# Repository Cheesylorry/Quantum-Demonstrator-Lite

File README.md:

# Quantum-Demonstrator-Lite
A Plug and play Quantum Algorithm Demonstrator for Students. Integrates into QuBeads, a software for visualising up to three Qubits, with fully customisable Quantum Gates.

*Picture of the Setup used at the Max Planck Institute of Quantum Optics*

The Quantum Demonstrator Lite can be used to demonstrate algorithms up to three Qubits over seven positions, and these can be viewed in Detail with the  QuBeads Software, available at https://spindrops.org/2.5.0-beta1/download.html *(We recommend going with the Beta, as it has the updated visualisation)*

    NOTE: The final product is to be used with QuBeads, the successor to SpinDrops. The auto Update is not available in SpinDrops but is on the ToDo for QuBeads.

The Quantum Demontrator Lite utilises 21 RC522 readers to maximise flexibility with the Quantum gates, allowing you to create your own custom gates. These are being controlled by a Raspberry Pi Pico2 Microcontroller, which in turn communicates with the PC over USB. 

It was designed to be somewhat affordable to institutions and Schools, with a price around 400€ depending of the suppliers you choose, and the means of assembly.

# Getting Started
For anybody wanting to build the Demonstrator, you should have a few prerequisite Tools:
| Tool | |
| --- | --- |
| 3D Printer | Ideally one with a Printbed bigger than 300x250, but 250x250 can also accomodate all parts. The ability to Print Mulit Colour is also very Helpful for printing the Gates|
| Soldering Iron | A fine tipped Soldering Station/Iron is necesary, should you decide to assemble the PCB yourself, Solder flux, tweezers, tin snips and more standard Soldering tools are required|
| Hex Bits | A standard Metric Set of Hex bits |

*Note: Should you decide to assemble the PCB yourself, be aware the SMD components are not the easiest to work with. A revamped version is a WIP which will drastically reduce the amount of components needed*

## Electronics
|[`Electronics/`](Electronics/README.md) contains the PCB Schematic and Board design. The PCB was designed in KiCad.
Parts needed for the PCB can be found via the Schematics, the BOM or here.

### Main PCB (Current state)
The current State is functional, but a simpler V2 is being worked on.

The Main PCB contains the Raspberry Pi Pico and all the power conversion needed to power the NFC readers, the LEDs and the Pi Pico itself.

| ID | Designator | Value/Component | Footprint | Qty | Source | Cost |
|:---:|:---|:---|:---|:---:|:---|:---:|
| 1 | A2 | Rapberry Pi Pico 2 | Pico SMD | 1 | [Conrad](https://www.conrad.de/de/p/raspberry-pi-pico-2-mikrocontroller-pico-2-3305690.html) | 5€ |
| 2 | Cbst1, Cbst2 | 100nF | 0805 SMD | 2 | [Supplier](URL) | |
| 3 | Cin1, Cin2  Cin3, Cin4 | 10µF | 0805 SMD | 4 | [Supplier](URL) | |
| 4 | Cout1, Cout2, Cout3 | 22µF | 0603 SMD | 3 | [Supplier](URL) | |
| 5 | Cout4 | 47µF | 1206 SMD | 1 | [Supplier](URL) | |
| 6 | F1 | 5A Fuse | 1206 SMD | 1 | [Supplier](URL) | |
| 7 | J1 | USB-C 16Pin | USB-C 16P | 1 | [Supplier](URL) | |
| 8 | J4 | Barrel Jack | Barrel Jack | 1 | [Digikey](https://www.digikey.de/de/products/detail/w%C3%BCrth-elektronik/694106301002/5047522?s=N4IgTCBcDaIGwE4AsBGADHAzG9aIF0BfIA) | 1€ |
| 9 | L1 | 2.2µH | ANR6045 SMD | 1 | [Supplier](URL) | |
| 10 | L2 | 4.7µH | 1008 SMD | 1 | [Supplier](URL) | |
| 11 | PCBconn1.1–3.2 | Molex Miligrid 4x2 | 08x04 THT | 4 | [Digikey](https://www.digikey.de/de/products/detail/molex/0878310820/679677) | 7,50€ |
| 12 | PCBconn1.1–3.2 | Molex Miligrid 4x2 | 08x04 THT | 2 | [Digikey](https://www.digikey.de/de/products/detail/molex/0878330831/2405183) | 5€ |
| 13 | R1, R2 | 5.1kΩ | 0805 SMD | 1 | [Supplier](URL) | |
| 14 | R3 | 160 Ω | 0805 SMD | 1 | [Supplier](URL) | |
| 15 | R6 | 100kΩ | 0805 SMD | 1 | [Supplier](URL) | |
| 16 | Rfbb1, Rfbb2 | 10kΩ | 0805 SMD | 2 | [Supplier](URL) | |
| 17 | Rfbt1 | 33.2kΩ | 0805 SMD | 1 | [Supplier](URL) | |
| 18 | Rfbt2 | 56.2kΩ | 0805 SMD | 1 | [Supplier](URL) | |
| 19 | SW2 | Switch with LED | R1966 SW SMD | 1 | [Digikey](https://www.digikey.de/de/products/detail/e-switch/R1966ABLKBLKESRED/251346?s=N4IgTCBcDaIEoEYCcA2FBBAQgGQNI9wFEBlOQgERAF0BfIA) | 2,50€ |
| 20 | U1 | TPS563200DDCR | SOT-23-6 SMD | 1 | [Supplier](URL) | |
| 21 | U2 | TPS561201DDCR | SOT-23-6 SMD | 1 | [Supplier](URL) | |

For a complete PCB assembbly service, you can expect to pay ~85€ 

Parts 1, 8, 11, 12 and 19 will have to be hand soldered. Numbers 8, 9 and 12 are Normal THT components, 19 has to be wired and then soldered.
The Raspberry Pi Pico2 has an Unusual way of soldering it to the PCB, due to the assumption one doesn't have a hotplate available.

| Top Side | Bottom Side |
|:--:|:--:|
||
||*Marked by the red Arrow are two through Holes, **these must be kept unfilled**, double check this when ordering the PCB* 

First solder down two of the SMD Pads of the Pi Pico, then turn the board around and fill the Marked through holes with solder, make sure to keep it warm for a bit, and probe the PCB for connection between the USB and the data pins on the Pi Pico.

### Connecting PCBs
The Quantum Demonstrator uses three almost identical PCBs to connect the individual NFC Readers to the Main PCB. These Connecting PCBs also mount the LEDs for the illumination. While all of the Connecting PCBs are the same, the Placement of the connectors is different for one of the three boards. 
These connectors are labeled with A.1, A.2 and B.1, B.2. This is neccessary due to cabeling and space saving.

**Two Boards must be configured with the A.1 and A.2 ports soldered and one Board with the B.1 and B.2 ports**

For all three Connection PCB, you will need:
| ID | Designator | Value/Component | Footprint | Qty | Source | Cost |
|:---:|:---|:---|:---|:---:|:---|:---:|
| 1 | LEDStrip1 5m | WS2815 12V LED Strip | 500x10mm | 1 | [Amazon](https://www.amazon.de/-/en/SEZO-Upgraded-Individually-Addressable-Non-Waterproof/dp/B0DNHVZDY6?) | 25€ |
| 2 | J2-J9 | Conn\_01x08\_Socket | THT | 30 | [Conrad](https://www.conrad.de/de/p/mpe-garry-stiftleiste-standard-anzahl-reihen-1-polzahl-je-reihe-8-087-1-008-0-s-xs0-1260-1-st-734023.html) | 5,50€ |
| 3 | PCBconnA.1 - A.2 | Conn\_02x04\_Counter\_Clockwise | THT | 6 | [Digikey](https://www.digikey.de/de/products/detail/molex/0878330831/2405183) | 13€ |

### Miscelaneous Parts
*Important Note for the NFC readers: **These must be the JoyIT readers, as the pinout is not compatible between different vendors.** The ones we specify have to have straight Through hole connectors, you can desolder the included conneectors or order via JoyIT directly and ask to have these connectors omitted, such that you can solder your own.*

| ID | Designator | Value/Component | Qty | Source | Cost |
|:---:|:---|:---|:---:|:---|:---:|
| 1 | NFC Reader | JoyIT RC522 | 21 | [Conrad](https://www.conrad.de/de/p/joy-it-sbc-rfid-rc522-rfid-set-1-st-1503746.html) | 112€ |
| 2 | Cables 218509-1083 | Molex Milligrid 02x08 locking | 6 | [Mouser](https://www.mouser.de/en/ProductDetail/Molex/218509-1083?qs=A6eO%252BMLsxmQCsrsfTUrgcg%3D%3D) | 25,15€ |
| 3 | NFC Tags | 38 mm - NTAG 213 - 180 Byte | 50 | [NFC-Tag-Shop](https://www.nfc-tag-shop.de/en/NFC-Sticker-PET-38-mm-NTAG-213-180-Byte-white/68261) | 29,50€ |

## Mechanical Construction
The Case for the Quantum Demonstrator is Mostly 3D Printed, with two extra Aluminium Extrusions for stability. 

Rccommended Print settings:
| | | | | | |
|:---|:---:|:---|:---:|:---|:---:|
| Material: | PLA or PETG | Print Bed: | Satin or Textured | Infill: | 10-15% Gyroid|
| Nozzle Size: | 0.4mm | Layer height: | 0.15mm | Supports: | Only on bed |

### Bill of Materials
| Item | Quantity | Description | Suplier | Costs |
|:---:|:---:|:---|:---|:---:|
| 1 | 1 | PCB Main | | 100€ |
| 2 | 3 | Conn PCB | | 43€ |
| 3 | 1 | Switch | | 2,50€ |
| 4 | 2 | 594 mm 2020 Profile| [Motedis](https://www.motedis.com/de/Aluprofil-20x20-B-Typ-Nut-6) | 9€ |
| 5 | 1 | 🔴 Front Centre | | |
| 6 | 1 | 🔴 Middle Centre | | |
| 7 | 1 | 🔴 Rear Centre | | |
| 8 | 1 | 🔴 Corner Shoulder 1 | | |
| 9 | 1 | 🔴 Middle Shoulder 1 | | |
| 10 | 2 | 🔴 Corner Shoulder 2 | | |
| 11 | 1 | 🔴 Corner Shoulder 3 | | |
| 12 | 1 | 🔴 Middle Shoulder 2 | | |
| 13 | 3 | 🔴 Feet | | |
| 14 | 1 | 🔴 Lid Part 1/3 | | |
| 15 | 1 | 🔴 Lid Part 3/1 | | |
| 16 | 1 | 🔴 Lid Part 2 | | |
| 17 | 31 | Hex screw M4x0.70 x 12 A2 | [Motedis](https://www.motedis.com/de/Zylinderschraube-mit-Innensechskant-nach-DIN-912/M4x12) | 4,17€ |
| 18 | 6 | Hex socket head cap screw M4x0.70 x 40 A2 | [Motedis](https://www.motedis.com/de/Sonderschraube-Stossverbinder-M4x40-180G-N5-I-Typ) | 1,70€ |
| 19 | 12 | Hex countersunk screw M4x0.70 x10 A2 | [Motedis](https://www.motedis.com/de/Senkschraube-mit-Innensechskant-nach-DIN-7991/M4x10) | 3,17€ |
| 20 | 2 | 🔴 Lidholder type 1 | | |
| 21 | 2 | 🔴 Lidholder type 2 | | |
| 22 | 2 | 🔴 Lidholder type 3 | | |
| 23 | 2 | PETG 3D-printing Filament | [Prusa3D]({https://www.prusa3d.com/product/prusament-petg-prusa-galaxy-black-1kg-nfc) | 58€ |
| 24 | 39 | Heatset Insert M4| [CNC Kitchen](https://cnckitchen.store/products/heat-set-insert-m4-x-4-short-version-100-pieces)|9,40€|
| 25 | xx | Heatset Insert M2|||
| 26 | xx | T-Nut6-M4  Bosch Rexroth compatible|||

*BOM of Assembly 1, List of Parts to 3D print marked in (🔴)*

*Todo: Link Parts in here to parts in Project*

On the Prusa XL this would need 4-5 Printbeds

## Assembly of the Case

### Heatset Inserts
In preperation for assembly, insert the threaded Heatset Inserts into the pre made holes.
For this set your soldering iron to aroun 250°C and slowly but firmly melt and press the insert into the hole. Try to keep it as level as possible to the Surface. The Following pcitures show where to position the Inserts.
| Top Side | Bottom Side |
|:--:|:--:|
||

### Connection to the Aluminium Extrusion

There are multiple screwholes from the outside accessing the Aluminium extrusion. Insert the Matching screw, at a T-Nut onto it, and slide it onto the Aluminium Extrusion. 
Start with the Shoulder Sections, then do the middle section, then the Feet to tie it all to gether. Only put the lid on right at the end.

### Mounting of PCBs
The Connection PCBs are screwed down with three M4 Screws, while the Main PCB is screwed down with three M2 screws.

### Installing LEDs
Glue the LED strip down on the marked region. Make sure the Pinout is correct, adn solder it to the given Pads.
To aid in diffusion a Thin plastic sheet is glued to the back of the Lid pieced to coder the Lighting slits (A piece of paper also works).

## Software
The Quantum Demonstrator requires some Embedded and some PC side software. 
### Prerequisites
| Software | |
| --- | --- |
| PlatformIO | A means to flash the C++ onto the RaspberryPi Pico via USB e.g. PlatformIO in VSCodium|
| Python 3.14| or newer. Needed for the PC Side software
| Tkinter 3.14 | or newer. Needed for the GUI on the PC side|

### Embedded Software
Flash the C++ Program [`main.cpp`](Embedded_Software/src/main.cpp) onto the Raspberry Pi Pico 2 via USB. 

### PC Side Software 
Download the [`PC_side_Software/`](/PC_side_Software/README.md) folder and run 

    python main.py          

Quick check without hardware or GUI:

    python selftest.py

**For a more in depth explaination:** [`/PC_side_Software/README.md`](/PC_side_Software/README.md)

## Constructing the Quantum Gates
Download the desired Gates from [`/CAD files/Quantum Gates/`](/CAD%20files/Quantum%20Gates/) and 3D print them. Then glue An NFC Tag into each Indent (on single Qubit gates only one, on Mulit Qubit gates two or even three)

# Using the Quantum Demonstrator (Work in Progress)
Connect the Demonstrator to 12V power and USB, and Turn it on
Start python main.py and select the USB device in the dropdown Menu, and check if you can see Gates appear when you place them on the readers.

"The Autowrite Json" automatically writes the JSON ever time an update is registered. This means you can continously import these files into spindrops.The directroy it deposits the files in can be chosen on launch.
Now Start spindrops and import the newly generated QD_output.json File.
Congratulations! You now have a functioning Quantum Demonstrator.

# Enrolling New Gates into the Database (Heavy Work in Progress)
Run
    python enroll.py --port /dev/ttyACM0
and then follow the instructions. The Names are only Important if you want to designate your own gates via the spin drops Syntax.

| Real World Gate | Database Shortname to use|
| --- | --- |
| Hadamard | **H**|
| Not | **X** |
| Phase | **Phase(*[deg]*)**|
| | | 

# Known Issues / ToDo
When enrolling gates the UUID gets entered incorrectly. *Fix: Use multiple reads and verify against each other* - Temporary fix, reenroll the gate.

## ToDo
- Add GUI to the enroll process
- Fix framing issues in gui.py
- Package as Binary
- Proper spindrops integration -> WIP

# Revamped PCB (HEAVY WIP)
to lower the costs of single piece production move from custom designed Voltage conversion to premade TRACOS.

Staged Design 12V -> 5V -> 3.3? vs Drirect Design 12V -> 5V and 12V -> 3.3V

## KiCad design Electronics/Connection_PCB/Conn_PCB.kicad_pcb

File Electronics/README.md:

Parts needed for the PCB can be found via the Schematics, the BOM or here.

| ID | Designator | Value/Component | Footprint | Qty | Source | Cost |
|:---:|:---|:---|:---|:---:|:---|:---:|
| 1 | A2 | Rapberry Pi Pico 2 | Pico SMD | 1 | [Conrad](https://www.conrad.de/de/p/raspberry-pi-pico-2-mikrocontroller-pico-2-3305690.html) | 5€ |
| 2 | Cbst1, Cbst2 | 100nF | 0805 SMD | 2 | [Supplier](URL) | |
| 3 | Cin1, Cin2  Cin3, Cin4 | 10µF | 0805 SMD | 2 | [Supplier](URL) | |
| 4 | Cout1, Cout2, Cout3 | 22µF | 0603 SMD | 3 | [Supplier](URL) | |
| 5 | Cout4 | 47µF | 1206 SMD | 1 | [Supplier](URL) | |
| 6 | F1 | 5A Fuse | 1206 SMD | 1 | [Supplier](URL) | |
| 7 | J1 | USB-C 16Pin | USB-C 16P | 1 | [Supplier](URL) | |
| 8 | J4 | Barrel Jack | Barrel Jack | 1 | [Digikey](https://www.digikey.de/de/products/detail/w%C3%BCrth-elektronik/694106301002/5047522?s=N4IgTCBcDaIGwE4AsBGADHAzG9aIF0BfIA) | 1€ |
| 9 | L1 | 2.2µH | ANR6045 SMD | 1 | [Supplier](URL) | |
| 10 | L2 | 4.7µH | 1008 SMD | 1 | [Supplier](URL) | |
| 11 | PCBconn1.1–3.2 | Molex Miligrid 4x2 | 08x04 THT | 4 | [Digikey](https://www.digikey.de/de/products/detail/molex/0878310820/679677) | 7,50€ |
| 12 | PCBconn1.1–3.2 | Molex Miligrid 4x2 | 08x04 THT | 2 | [Digikey](https://www.digikey.de/de/products/detail/molex/0878330831/2405183) | 5€ |
| 13 | R1, R2 | 5.1kΩ | 0805 SMD | 1 | [Supplier](URL) | |
| 14 | R3 | 160 Ω | 0805 SMD | 1 | [Supplier](URL) | |
| 15 | R6 | 100kΩ | 0805 SMD | 1 | [Supplier](URL) | |
| 16 | Rfbb1, Rfbb2 | 10kΩ | 0805 SMD | 2 | [Supplier](URL) | |
| 17 | Rfbt1 | 33.2kΩ | 0805 SMD | 1 | [Supplier](URL) | |
| 18 | Rfbt2 | 56.2kΩ | 0805 SMD | 1 | [Supplier](URL) | |
| 19 | SW2 | Switch with LED | R1966 SW SMD | 1 | [Digikey](https://www.digikey.de/de/products/detail/e-switch/R1966ABLKBLKESRED/251346?s=N4IgTCBcDaIEoEYCcA2FBBAQgGQNI9wFEBlOQgERAF0BfIA) | 2,50€ |
| 20 | U1 | TPS563200DDCR | SOT-23-6 SMD | 1 | [Supplier](URL) | |
| 21 | U2 | TPS561201DDCR | SOT-23-6 SMD | 1 | [Supplier](URL) | |

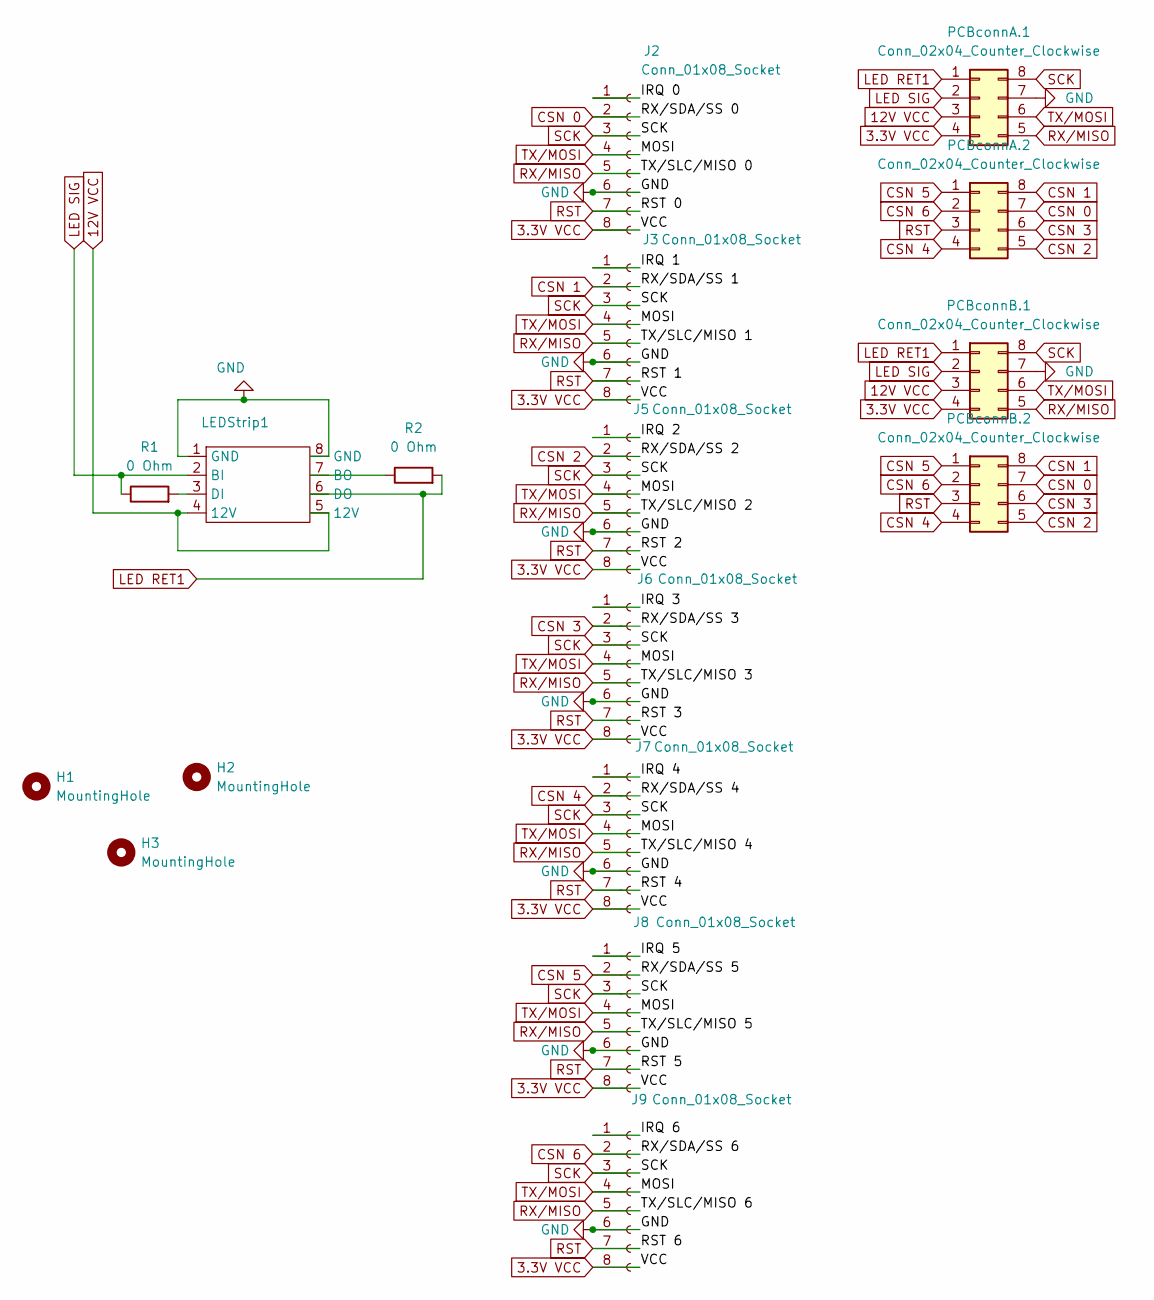
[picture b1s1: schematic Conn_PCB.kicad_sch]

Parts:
H1, H2: MountingHole; MountingHole_4.3x6.2mm_M4_Pad_Via
H3: MountingHole; MountingHole_4.3mm_M4_ISO14580_Pad
J2, J3, J5, J6, J7, J8, J9: Conn_01x08_Socket; PinSocket_1x08_P2.54mm_Vertical
LEDStrip1: LED strip Pad 2815
PCBconnA.1, PCBconnA.2: Conn_02x04_Counter_Clockwise; CONN08_878310820_MOL_Milli_grid
PCBconnB.1, PCBconnB.2: Conn_02x04_Counter_Clockwise; CONN08_878310820_MOL_Milli_grid
R1, R2: 0 Ohm; R_0603_1608Metric_Pad0.98x0.95mm_HandSolder

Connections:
3.3V VCC: J2.8, J3.8, J5.8, J6.8, J7.8, J8.8, J9.8, PCBconnA.1.4, PCBconnB.1.4
12V VCC: LEDStrip1.4 (12V), LEDStrip1.5 (12V), PCBconnA.1.3, PCBconnB.1.3
/IRQ 0: J2.1
/IRQ 1: J3.1
/IRQ 2: J5.1
/IRQ 3: J6.1
/IRQ 4: J7.1
/IRQ 5: J8.1
/IRQ 6: J9.1
CSN 0: J2.2, PCBconnA.2.7, PCBconnB.2.7
CSN 1: J3.2, PCBconnA.2.8, PCBconnB.2.8
CSN 2: J5.2, PCBconnA.2.5, PCBconnB.2.5
CSN 3: J6.2, PCBconnA.2.6, PCBconnB.2.6
CSN 4: J7.2, PCBconnA.2.4, PCBconnB.2.4
CSN 5: J8.2, PCBconnA.2.1, PCBconnB.2.1
CSN 6: J9.2, PCBconnA.2.2, PCBconnB.2.2
GND: J2.6, J3.6, J5.6, J6.6, J7.6, J8.6, J9.6, LEDStrip1.1 (GND), LEDStrip1.8 (GND), PCBconnA.1.7, PCBconnB.1.7
LED RET1: LEDStrip1.6 (DO), PCBconnA.1.1, PCBconnB.1.1, R2.2
LED SIG: LEDStrip1.2 (BI), PCBconnA.1.2, PCBconnB.1.2, R1.1
unnamed: LEDStrip1.7 (BO), R2.1
unnamed: LEDStrip1.3 (DI), R1.2
RST: J2.7, J3.7, J5.7, J6.7, J7.7, J8.7, J9.7, PCBconnA.2.3, PCBconnB.2.3
RX/MISO: J2.5, J3.5, J5.5, J6.5, J7.5, J8.5, J9.5, PCBconnA.1.5, PCBconnB.1.5
SCK: J2.3, J3.3, J5.3, J6.3, J7.3, J8.3, J9.3, PCBconnA.1.8, PCBconnB.1.8
TX/MOSI: J2.4, J3.4, J5.4, J6.4, J7.4, J8.4, J9.4, PCBconnA.1.6, PCBconnB.1.6

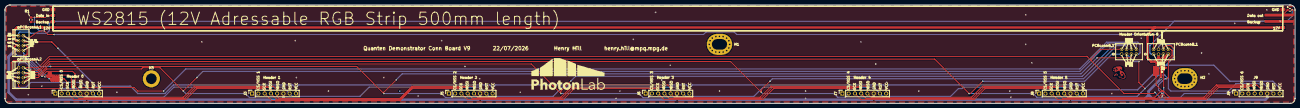
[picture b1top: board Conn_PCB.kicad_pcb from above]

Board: 2 copper layers, 524.5 x 40.0 mm, 17 parts (0 on the bottom side), 18 nets.

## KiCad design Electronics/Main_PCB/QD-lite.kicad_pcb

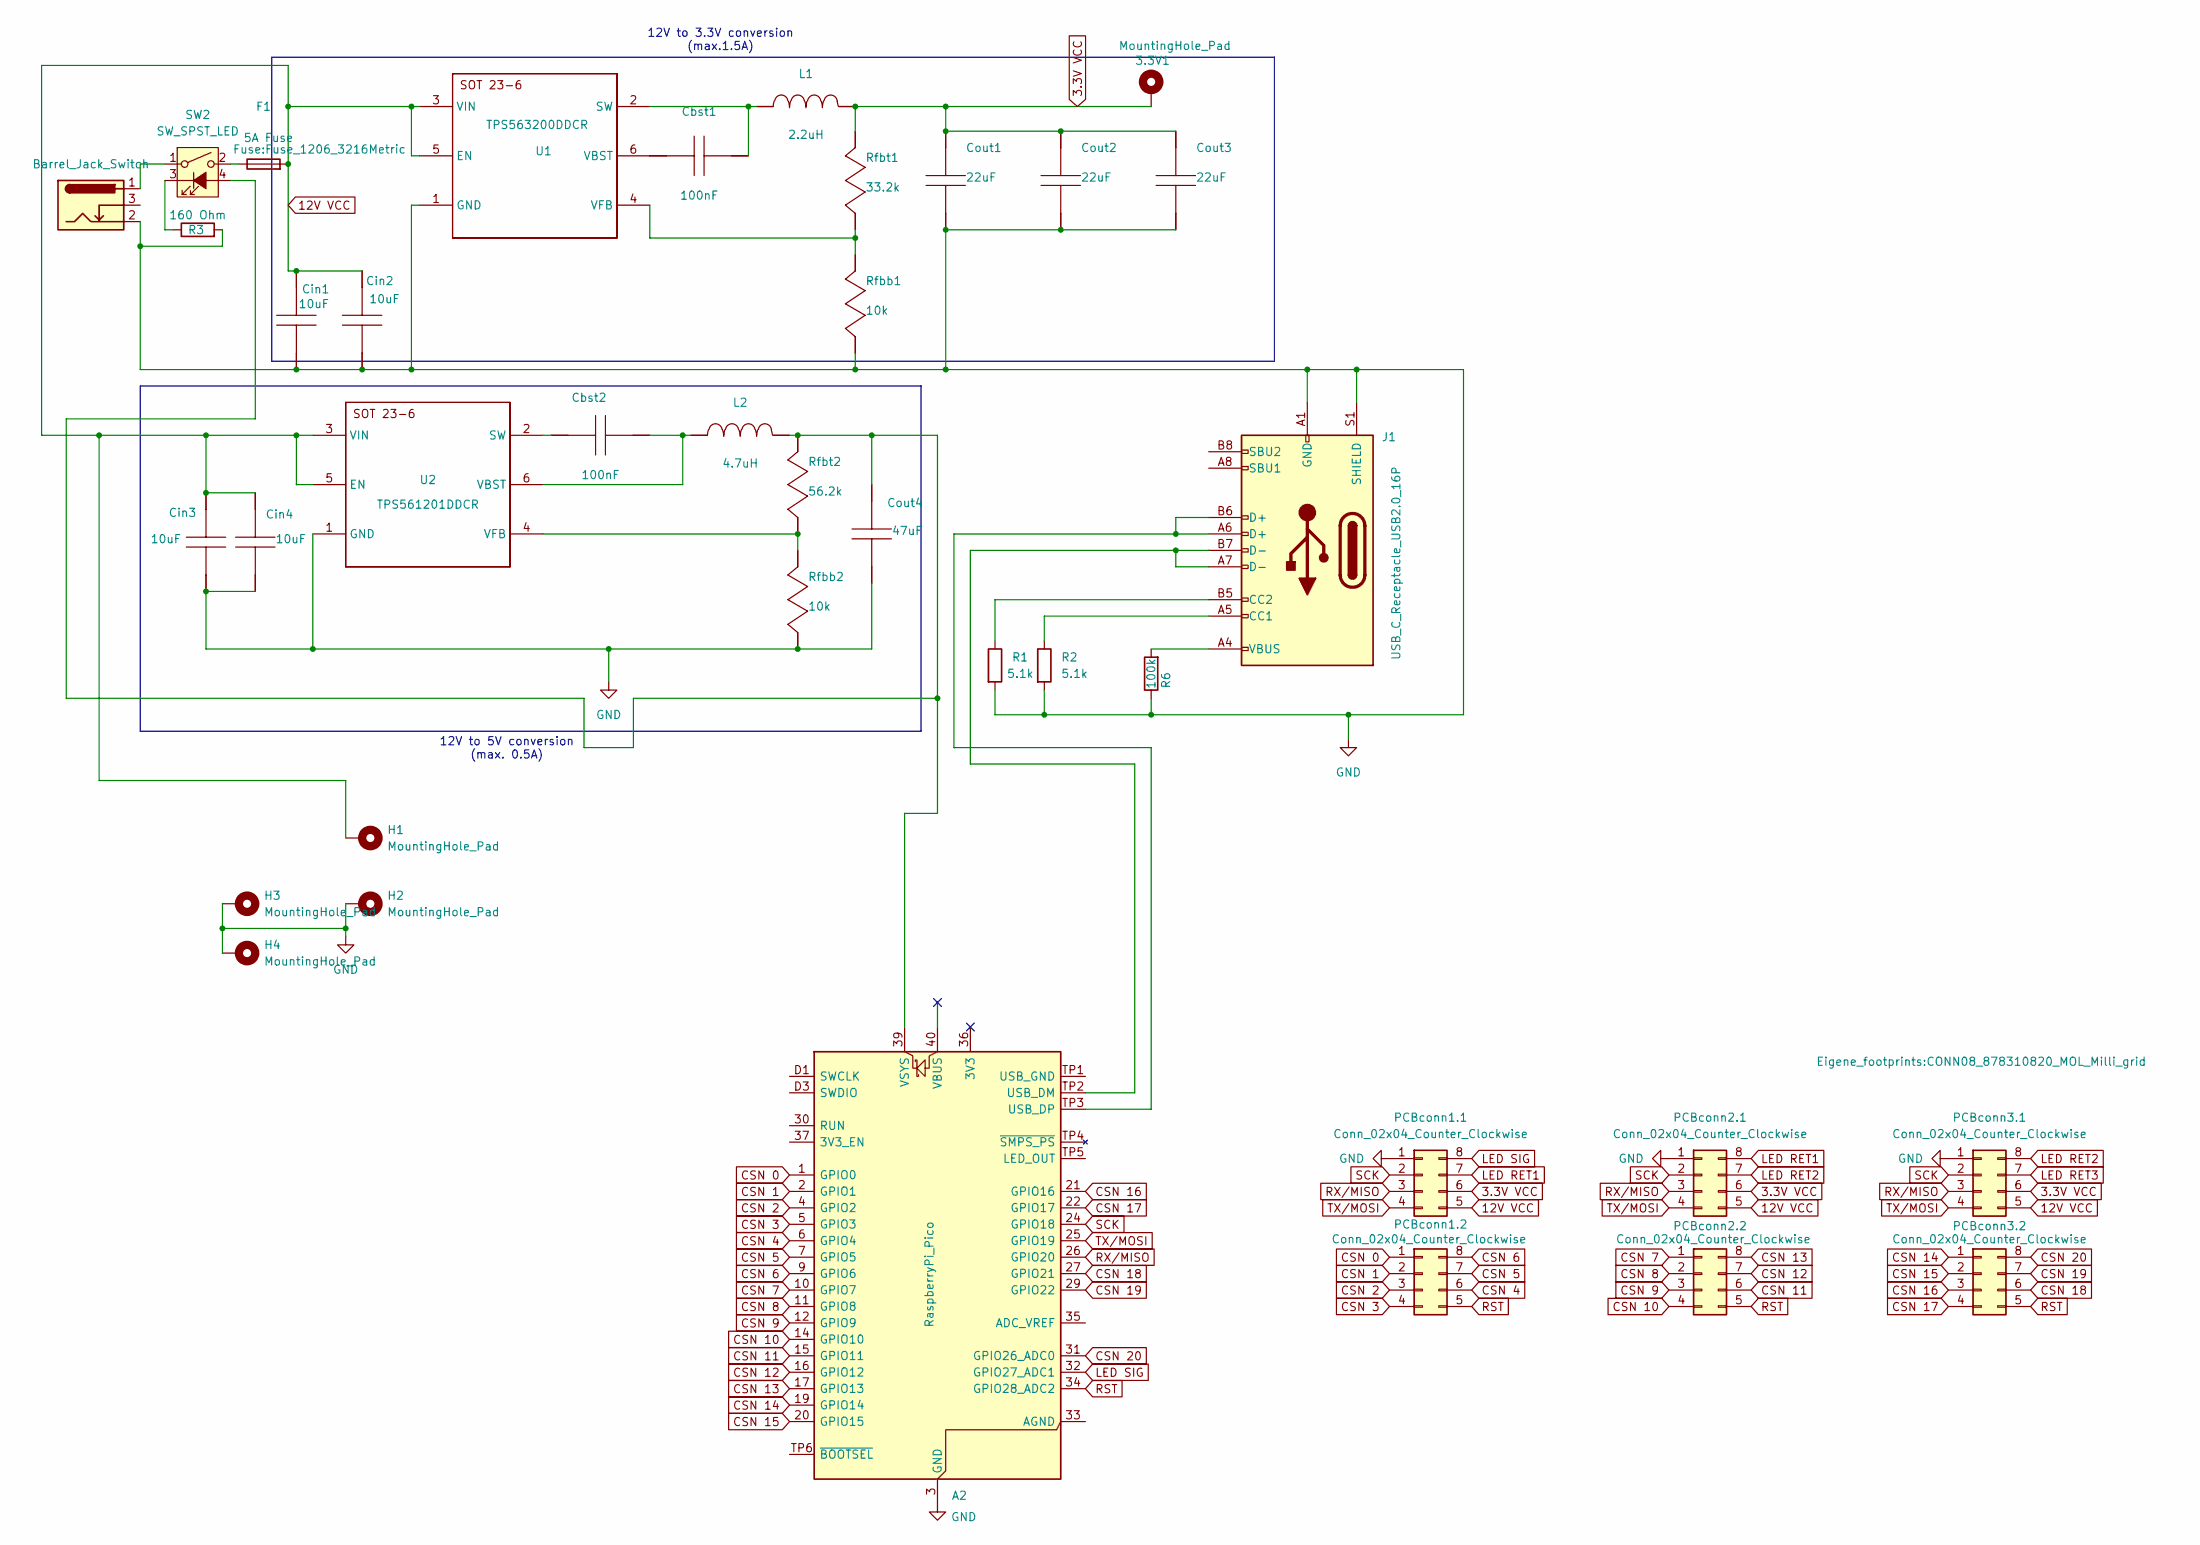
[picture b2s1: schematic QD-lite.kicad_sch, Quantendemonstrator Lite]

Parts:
3.3V1: MountingHole_Pad; MountingHole_2.5mm_Pad_Via
A2: RaspberryPi_Pico; RaspberryPi_Pico_SMD
Cbst1, Cbst2: 08053C104KAT2A; C_0805_2012Metric_Pad1.18x1.45mm_HandSolder; MANUFACTURER PART NUMBER 08053C104KAT2A
Cin1, Cin2: MSAST219LB5106KTNA01; C_0805_2012Metric_Pad1.18x1.45mm_HandSolder; MANUFACTURER PART NUMBER MSAST219LB5106KTNA01
Cin3, Cin4: MSAST219LB5106KTNA01; C_0805_2012Metric_Pad1.18x1.45mm_HandSolder; MANUFACTURER PART NUMBER MSAST21GBB5106MTNA01
Cout1, Cout2, Cout3: GRM188R60J226MEA0D; C_0603_1608Metric_Pad1.08x0.95mm_HandSolder; MANUFACTURER PART NUMBER GRM188R60J226MEA0D
Cout4: C3216X5R1C476M160AB; C_1206_3216Metric_Pad1.33x1.80mm_HandSolder; MANUFACTURER PART NUMBER C3216X5R1C476M160AB
F1: 5A Fuse; Fuse_1206_3216Metric
H1, H2: MountingHole_Pad; MountingHole_2.2mm_M2_DIN965_Pad_TopBottom
H3, H4: MountingHole_Pad; MountingHole_2.7mm_M2.5_Pad_Via
J1: USB_C_Receptacle_USB2.0_16P; USB_C_Receptacle_GCT_USB4105-xx-A_16P_TopMnt_Horizontal
J4: Barrel_Jack_Switch; BarrelJack_Wuerth_6941xx301002_CAD
L1: VLS6045EX-2R2N; L_APV_ANR6045; MANUFACTURER PART NUMBER VLP8040T-2R2N
L2: LQM2HPN4R7MG0L; L_1008_2520Metric_Pad1.43x2.20mm_HandSolder; MANUFACTURER PART NUMBER LQM2HPN4R7MG0L
PCBconn1.1, PCBconn1.2, PCBconn2.1, PCBconn2.2, PCBconn3.1, PCBconn3.2: Conn_02x04_Counter_Clockwise; CONN08_878310820_MOL_Milli_grid
R1: 5.1k; R_0805_2012Metric_Pad1.20x1.40mm_HandSolder
R2: 5.1k; R_0805_2012Metric
R3: 160 Ohm; R_0805_2012Metric_Pad1.20x1.40mm_HandSolder
R6: 100k; R_0805_2012Metric
Rfbb1, Rfbb2: RC0805FR-0710KL; R_0805_2012Metric_Pad1.20x1.40mm_HandSolder; MANUFACTURER PART NUMBER RC0805FR-0710KL
Rfbt1: CRCW080533K2FKEA; R_0805_2012Metric_Pad1.20x1.40mm_HandSolder; MANUFACTURER PART NUMBER CRCW080533K2FKEA
Rfbt2: RC0805FR-0756K2L; R_0805_2012Metric_Pad1.20x1.40mm_HandSolder; MANUFACTURER PART NUMBER RC0805FR-0756K2L
SW2: SW_SPST_LED; R1966ABLKBLKESRED footprint
U1: TPS563200DDCR; SOT-23-6; MANUFACTURER PART NUMBER TPS563209DDCR
U2: TPS561201DDCR; SOT-23-6; MANUFACTURER PART NUMBER TPS561201DDCR

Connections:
3.3V VCC: 3.3V1.1 (1_1), Cout1.1, Cout2.1, Cout3.1, L1.2, PCBconn1.1.6, PCBconn2.1.6, PCBconn3.1.6, Rfbt1.1
12V VCC: Cin1.1, Cin2.1, Cin3.1, Cin4.1, F1.2, H1.1 (1_1), PCBconn1.1.5, PCBconn2.1.5, PCBconn3.1.5, U1.3 (VIN), U1.5 (EN), U2.3 (VIN), U2.5 (EN)
CSN 0: A2.1 (GPIO0), PCBconn1.2.1
CSN 1: A2.2 (GPIO1), PCBconn1.2.2
CSN 2: A2.4 (GPIO2), PCBconn1.2.3
CSN 3: A2.5 (GPIO3), PCBconn1.2.4
CSN 4: A2.6 (GPIO4), PCBconn1.2.6
CSN 5: A2.7 (GPIO5), PCBconn1.2.7
CSN 6: A2.9 (GPIO6), PCBconn1.2.8
CSN 7: A2.10 (GPIO7), PCBconn2.2.1
CSN 8: A2.11 (GPIO8), PCBconn2.2.2
CSN 9: A2.12 (GPIO9), PCBconn2.2.3
CSN 10: A2.14 (GPIO10), PCBconn2.2.4
CSN 11: A2.15 (GPIO11), PCBconn2.2.6
CSN 12: A2.16 (GPIO12), PCBconn2.2.7
CSN 13: A2.17 (GPIO13), PCBconn2.2.8
CSN 14: A2.19 (GPIO14), PCBconn3.2.1
CSN 15: A2.20 (GPIO15), PCBconn3.2.2
CSN 16: A2.21 (GPIO16), PCBconn3.2.3
CSN 17: A2.22 (GPIO17), PCBconn3.2.4
CSN 18: A2.27 (GPIO21), PCBconn3.2.6
CSN 19: A2.29 (GPIO22), PCBconn3.2.7
CSN 20: A2.31 (GPIO26_ADC0), PCBconn3.2.8
GND: A2.3 (GND), A2.8 (GND), A2.13 (GND), A2.18 (GND), A2.23 (GND), A2.28 (GND), A2.38 (GND), A2.D2 (GND), Cin1.2, Cin2.2, Cin3.2, Cin4.2, Cout1.2, Cout2.2, Cout3.2, Cout4.2, H2.1 (1_1), H3.1 (1_1), H4.1 (1_1), J1.A1 (GND), J1.A12 (GND), J1.B1 (GND), J1.B12 (GND), J1.S1 (SHIELD), J4.2, PCBconn1.1.1, PCBconn2.1.1, PCBconn3.1.1, R1.2, R2.2, R3.2, R6.1, Rfbb1.2, Rfbb2.2, U1.1 (GND), U2.1 (GND)
LED RET1: PCBconn1.1.7, PCBconn2.1.8
LED RET2: PCBconn2.1.7, PCBconn3.1.8
LED RET3: PCBconn3.1.7
LED SIG: A2.32 (GPIO27_ADC1), PCBconn1.1.8
unnamed: A2.TP2 (USB_DM), J1.A7 (D-), J1.B7 (D-)
unnamed: A2.TP3 (USB_DP), J1.A6 (D+), J1.B6 (D+)
unnamed: A2.39 (VSYS), Cout4.1, L2.2, Rfbt2.1, SW2.4 (A)
unnamed: F1.1, SW2.2
unnamed: J1.A5 (CC1), R2.1
unnamed: J1.B5 (CC2), R1.1
unnamed: J1.A4 (VBUS), J1.A9 (VBUS), J1.B4 (VBUS), J1.B9 (VBUS), R6.2
unnamed: J4.1, SW2.1
unnamed: R3.1, SW2.3 (K)
unnamed: Cbst1.1, L1.1, U1.2 (SW)
unnamed: Cbst1.2, U1.6 (VBST)
unnamed: Rfbb1.1, Rfbt1.2, U1.4 (VFB)
unnamed: Cbst2.2, U2.2 (SW)
unnamed: Cbst2.1, L2.1, U2.6 (VBST)
unnamed: Rfbb2.1, Rfbt2.2, U2.4 (VFB)
RST: A2.34 (GPIO28_ADC2), PCBconn1.2.5, PCBconn2.2.5, PCBconn3.2.5
RX/MISO: A2.26 (GPIO20), PCBconn1.1.3, PCBconn2.1.3, PCBconn3.1.3
SCK: A2.24 (GPIO18), PCBconn1.1.2, PCBconn2.1.2, PCBconn3.1.2
TX/MOSI: A2.25 (GPIO19), PCBconn1.1.4, PCBconn2.1.4, PCBconn3.1.4

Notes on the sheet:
12V to 3.3V conversion (max.1.5A)
12V to 5V conversion (max. 0.5A)

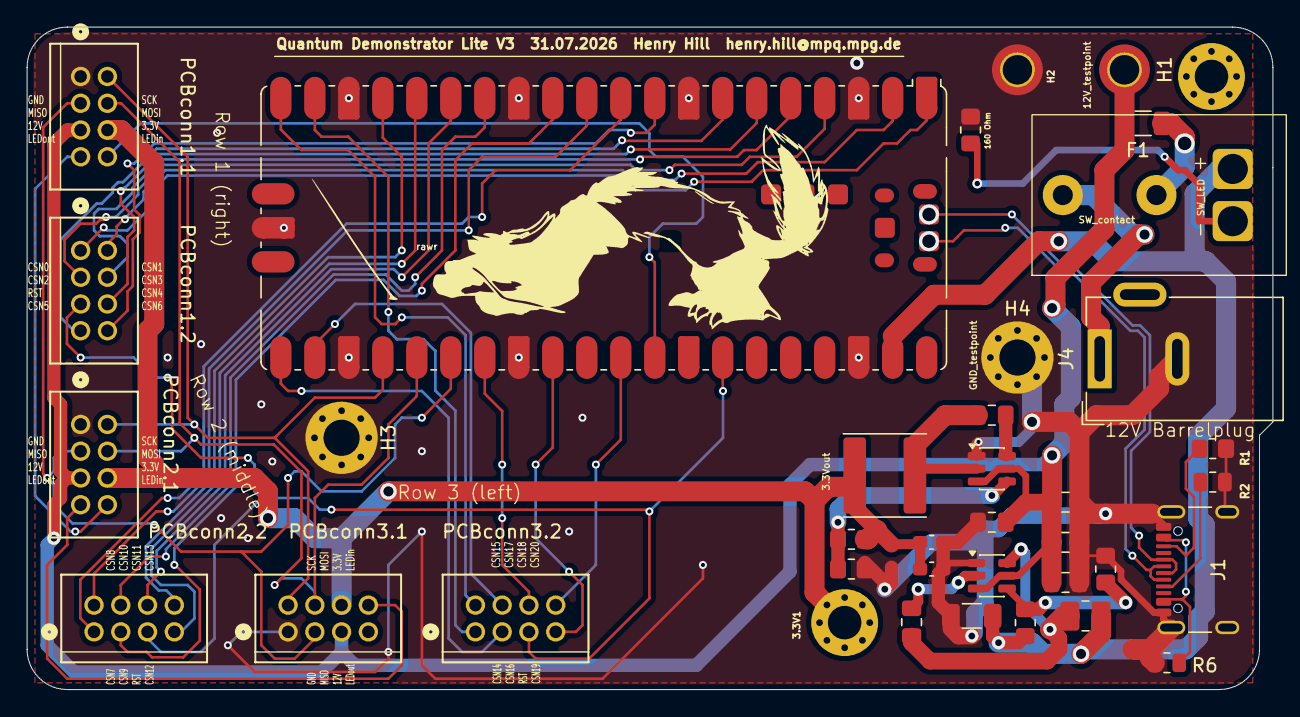
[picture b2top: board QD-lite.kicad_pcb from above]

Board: 2 copper layers, 93.1 x 49.5 mm, 39 parts (1 on the bottom side), 46 nets.

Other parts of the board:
M2.5: MountingHole_2.5mm_Pad_Via
